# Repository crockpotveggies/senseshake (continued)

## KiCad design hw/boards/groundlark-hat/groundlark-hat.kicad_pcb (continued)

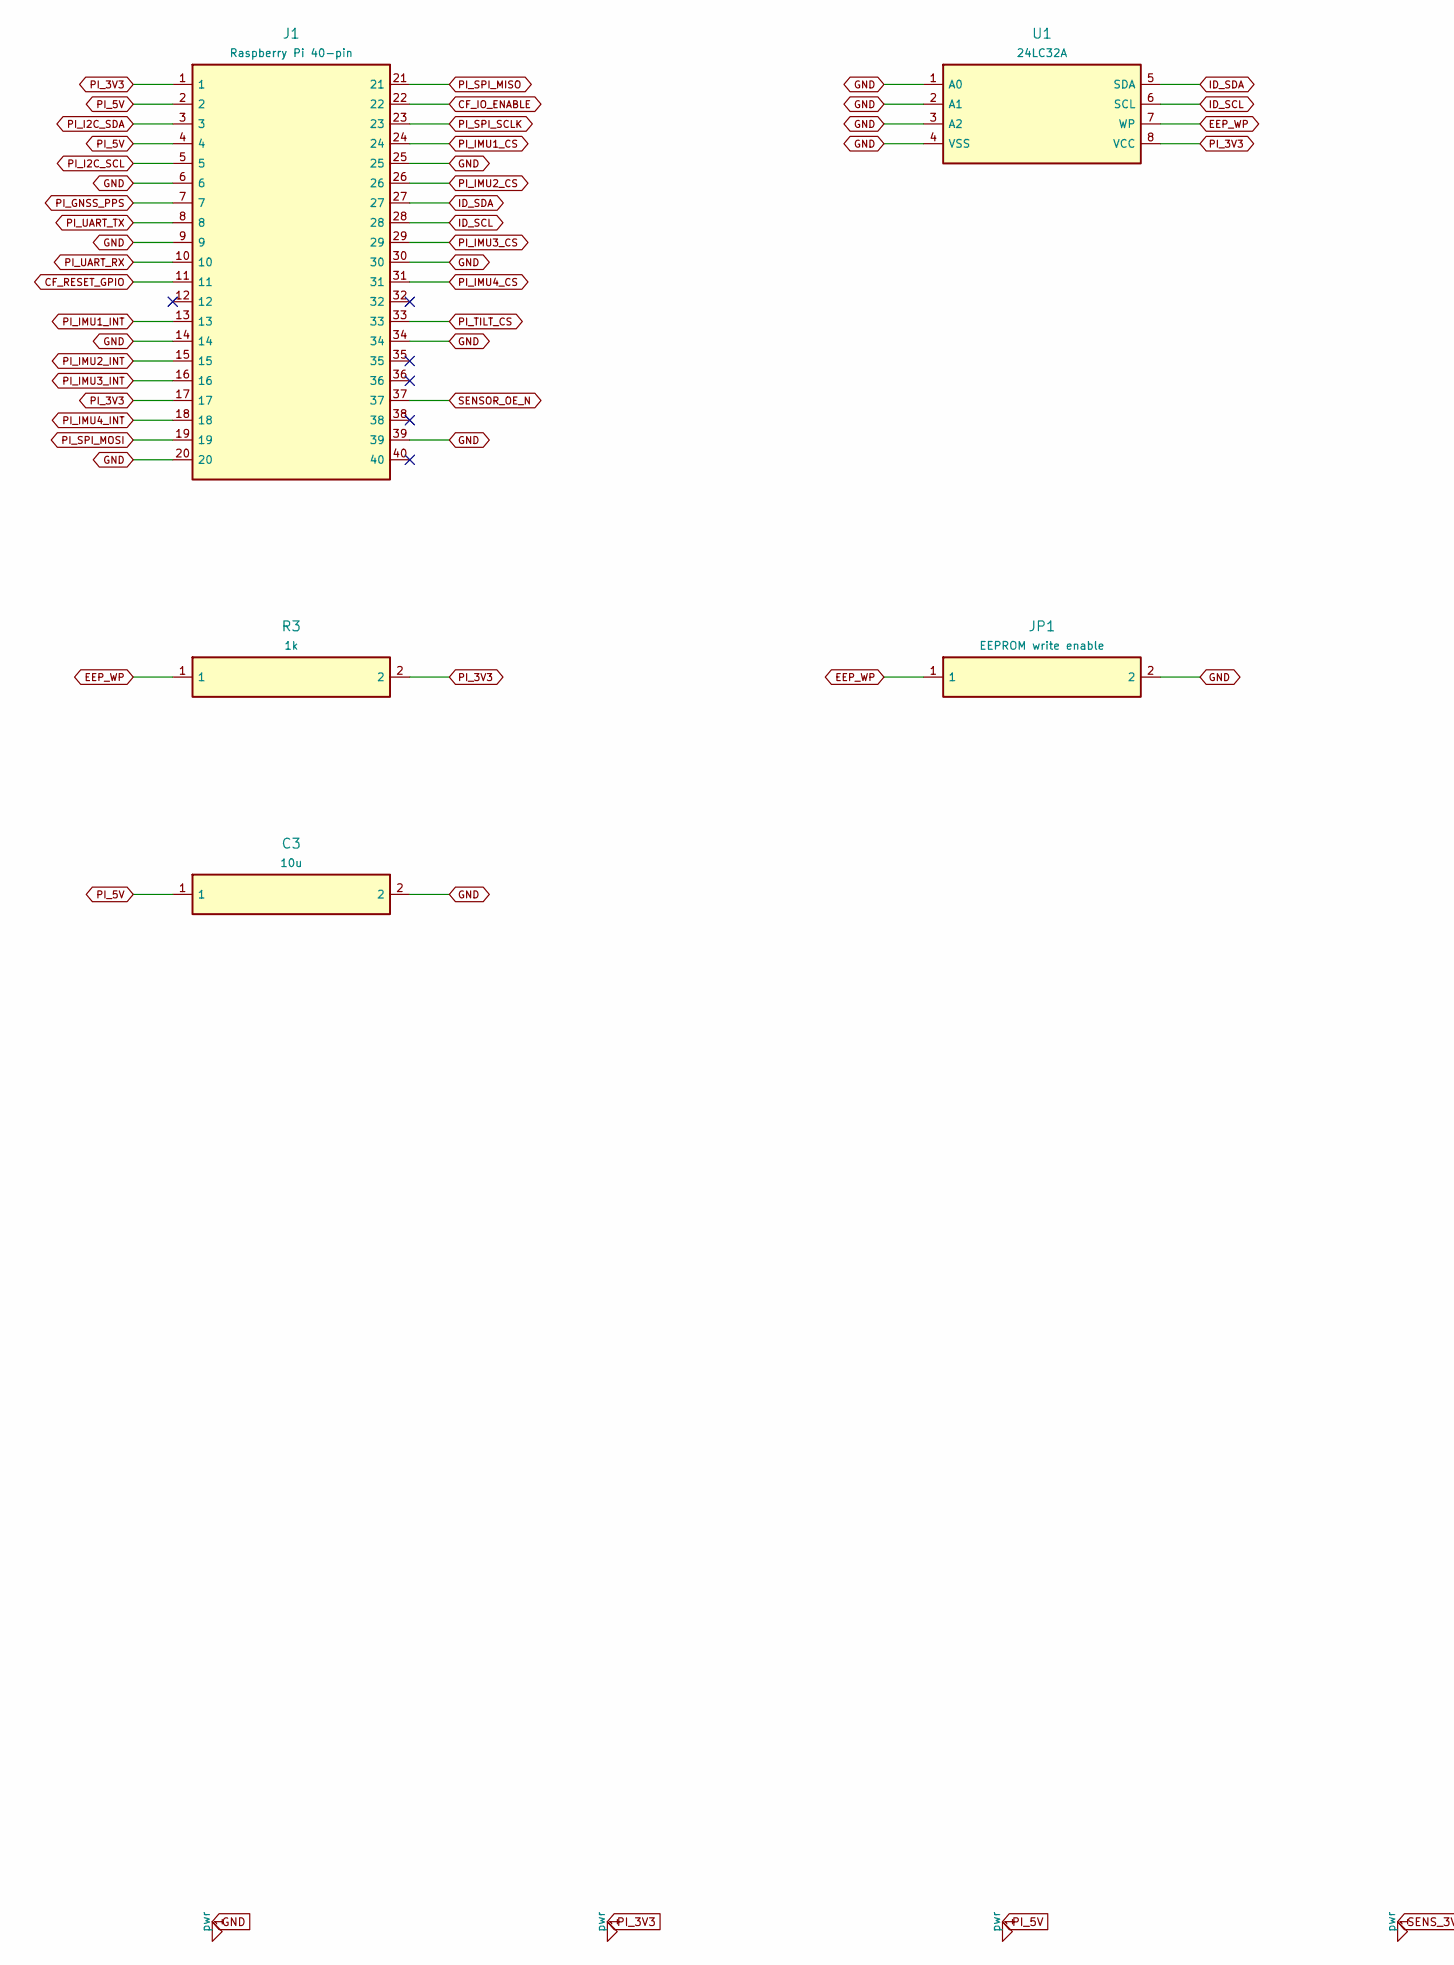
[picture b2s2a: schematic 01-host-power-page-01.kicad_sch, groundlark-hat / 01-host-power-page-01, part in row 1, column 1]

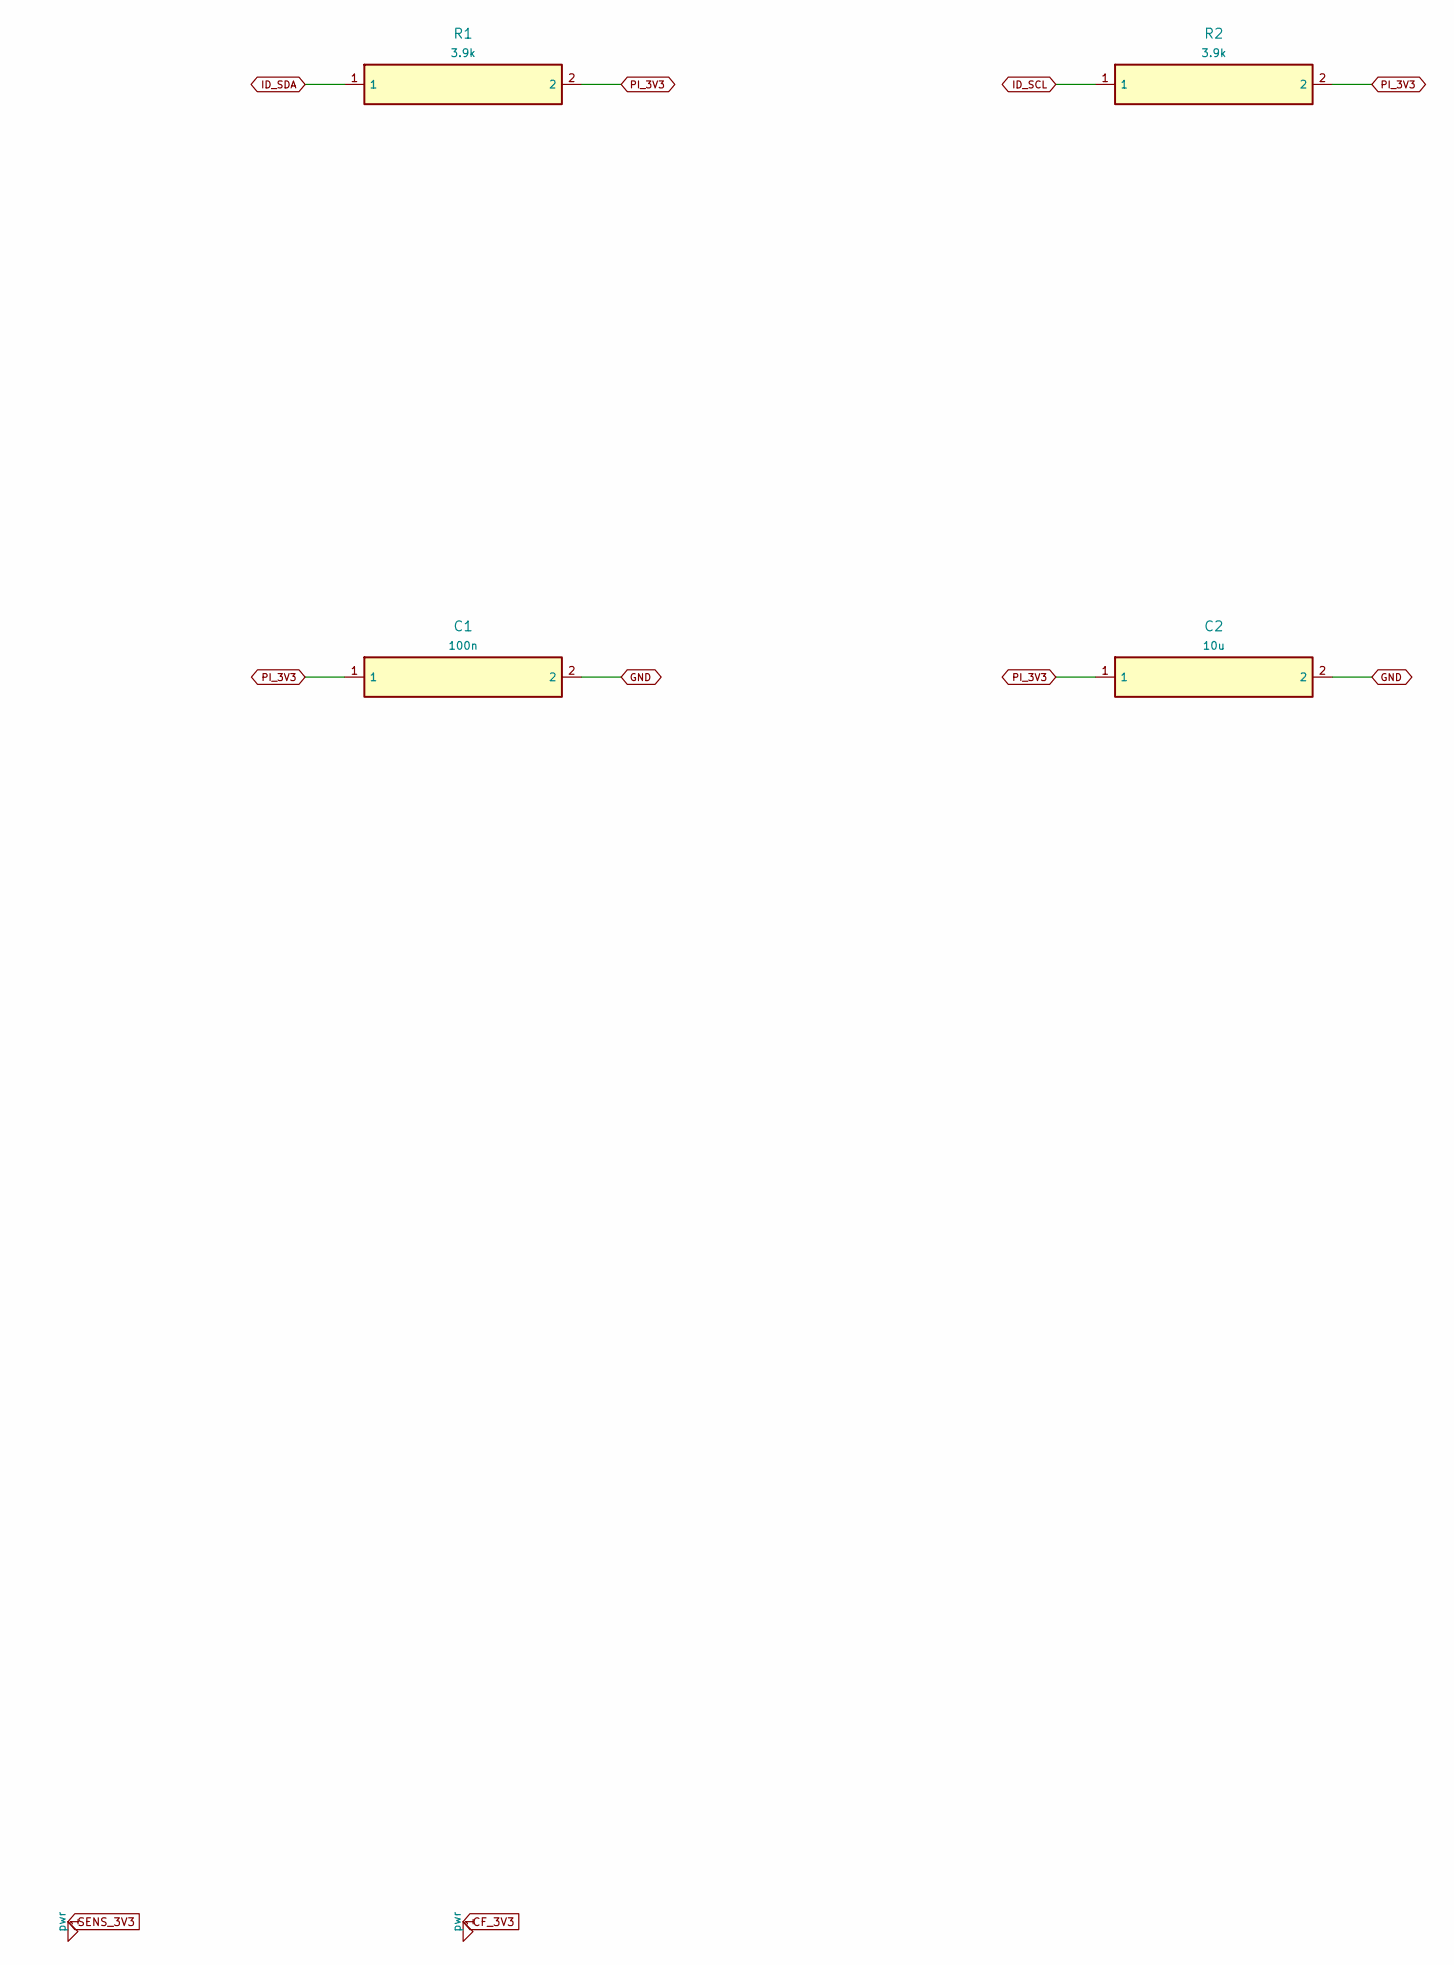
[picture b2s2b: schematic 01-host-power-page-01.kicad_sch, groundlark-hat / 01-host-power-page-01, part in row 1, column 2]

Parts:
C1: 100n; Capacitor_SMD__C_0603_1608Metric; MPN GRM188R71H104KA93D
C2, C3: 10u; Capacitor_SMD__C_0805_2012Metric; MPN GRM21BR61A106KE19L
J1: Raspberry Pi 40-pin; Connector_PinHeader_2.54mm__PinHeader_2x20_P2.54mm_Vertical; MPN Samtec ESQ-120-23-G-D
JP1: EEPROM write enable; Connector_PinHeader_2.54mm__PinHeader_1x02_P2.54mm_Vertical; MPN EEPROM write enable
R1, R2: 3.9k; Resistor_SMD__R_0603_1608Metric; MPN RC0603FR-073K9L
R3: 1k; Resistor_SMD__R_0603_1608Metric; MPN RC0603FR-071KL
U1: 24LC32A; Package_SO__SOIC-8_3.9x4.9mm_P1.27mm; MPN 24LC32A-I/SN

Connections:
12: J1.12
32: J1.32
35: J1.35
36: J1.36
38: J1.38
40: J1.40
CF_IO_ENABLE: J1.22; also elsewhere on the board
CF_RESET_GPIO: J1.11; also elsewhere on the board
EEP_WP: JP1.1, R3.1, U1.7 (WP)
GND: C1.2, C2.2, C3.2, J1.6, J1.9, J1.14, J1.20, J1.25, J1.30, J1.34, J1.39, JP1.2, U1.1 (A0), U1.2 (A1), U1.3 (A2), U1.4 (VSS); also elsewhere on the board
ID_SCL: J1.28, R2.1, U1.6 (SCL)
ID_SDA: J1.27, R1.1, U1.5 (SDA)
PI_3V3: C1.1, C2.1, J1.1, J1.17, R1.2, R2.2, R3.2, U1.8 (VCC); also elsewhere on the board
PI_5V: C3.1, J1.2, J1.4; also elsewhere on the board
PI_GNSS_PPS: J1.7; also elsewhere on the board
PI_I2C_SCL: J1.5; also elsewhere on the board
PI_I2C_SDA: J1.3; also elsewhere on the board
PI_IMU1_CS: J1.24; also elsewhere on the board
PI_IMU1_INT: J1.13; also elsewhere on the board
PI_IMU2_CS: J1.26; also elsewhere on the board
PI_IMU2_INT: J1.15; also elsewhere on the board
PI_IMU3_CS: J1.29; also elsewhere on the board
PI_IMU3_INT: J1.16; also elsewhere on the board
PI_IMU4_CS: J1.31; also elsewhere on the board
PI_IMU4_INT: J1.18; also elsewhere on the board
PI_SPI_MISO: J1.21; also elsewhere on the board
PI_SPI_MOSI: J1.19; also elsewhere on the board
PI_SPI_SCLK: J1.23; also elsewhere on the board
PI_TILT_CS: J1.33; also elsewhere on the board
PI_UART_RX: J1.10; also elsewhere on the board
PI_UART_TX: J1.8; also elsewhere on the board
SENSOR_OE_N: J1.37; also elsewhere on the board

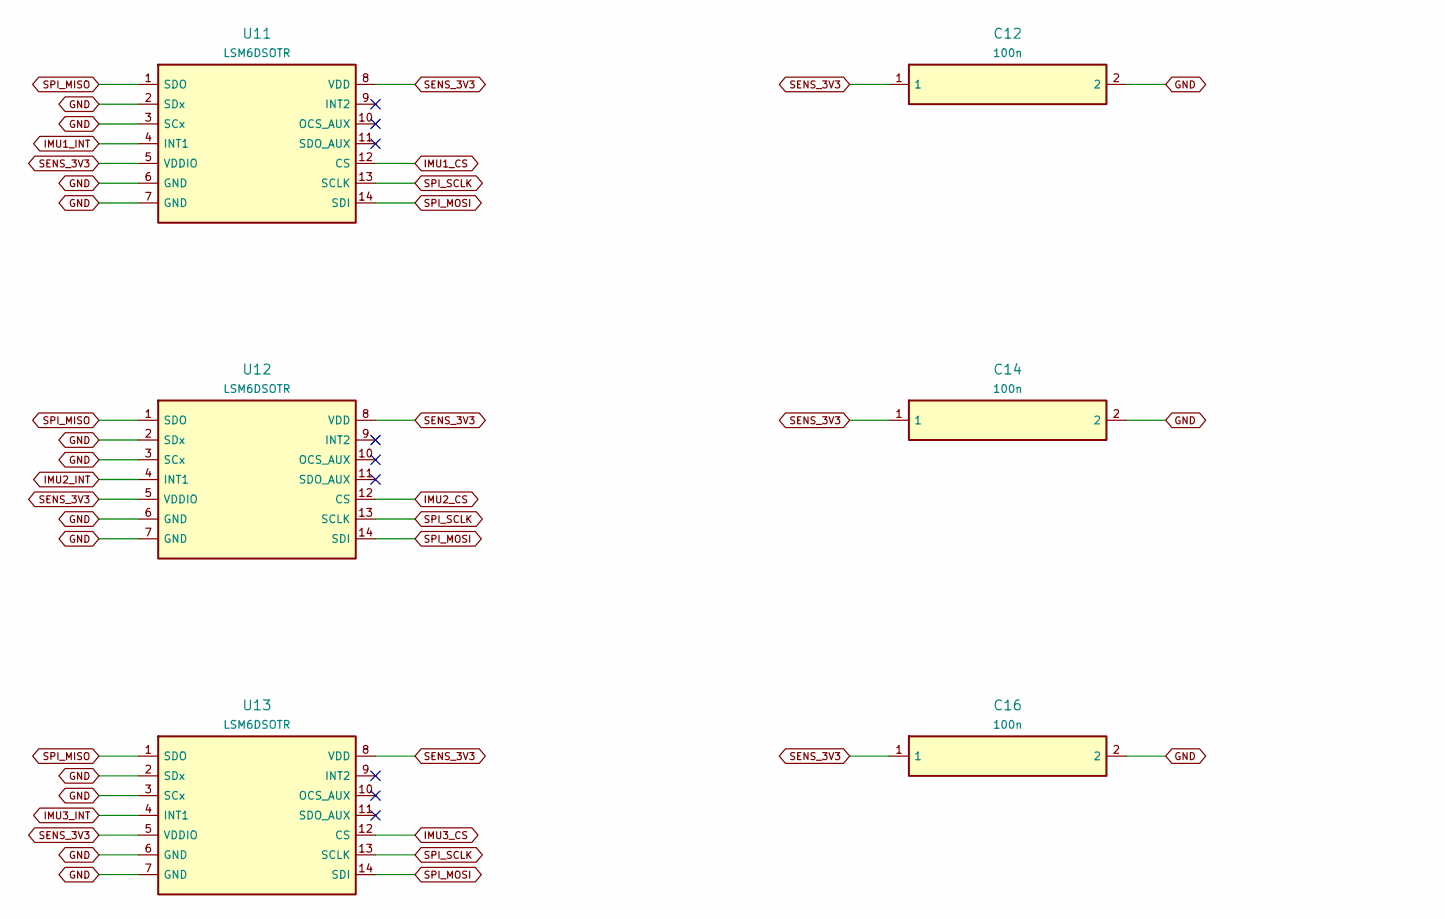
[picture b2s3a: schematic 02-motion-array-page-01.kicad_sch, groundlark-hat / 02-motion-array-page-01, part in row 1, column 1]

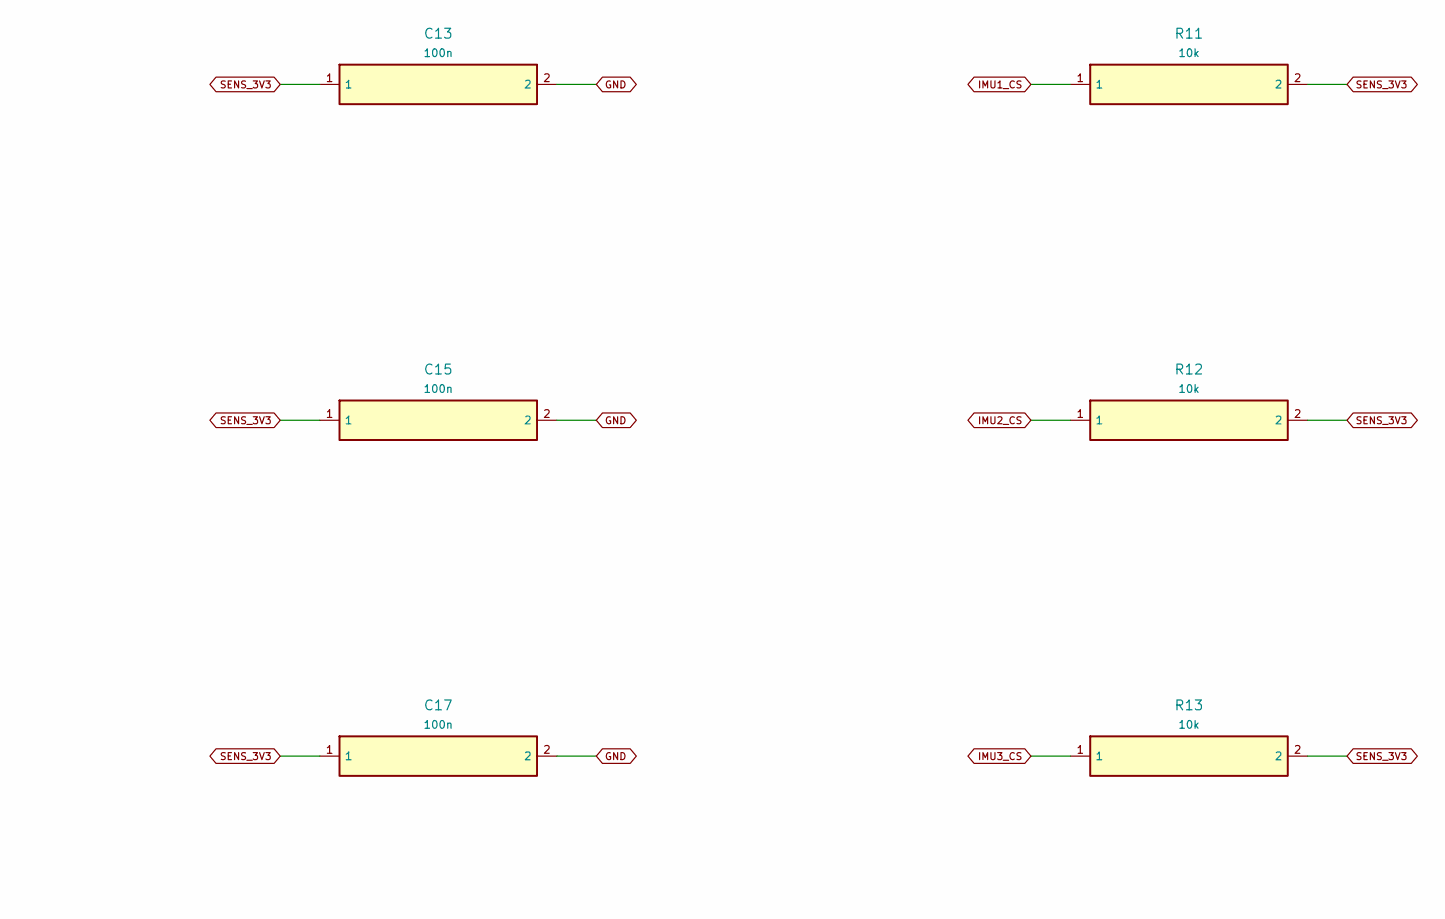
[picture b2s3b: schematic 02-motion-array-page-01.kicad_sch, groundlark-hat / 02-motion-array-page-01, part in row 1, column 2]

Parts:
C12, C13, C14, C15, C16, C17: 100n; Capacitor_SMD__C_0402_1005Metric; MPN GRM155R71C104KA88D
R11, R12, R13: 10k; Resistor_SMD__R_0603_1608Metric; MPN RC0603FR-0710KL
U11, U12, U13: LSM6DSOTR; Package_LGA__LGA-14_3x2.5mm_P0.5mm_LayoutBorder3x4y; MPN LSM6DSOTR

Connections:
9: U11.9 (INT2)
10: U11.10 (OCS_AUX)
11: U11.11 (SDO_AUX)
GND: C12.2, C13.2, C14.2, C15.2, C16.2, C17.2, U11.2 (SDx), U11.3 (SCx), U11.6 (GND), U11.7 (GND), U12.2 (SDx), U12.3 (SCx), U12.6 (GND), U12.7 (GND), U13.2 (SDx), U13.3 (SCx), U13.6 (GND), U13.7 (GND); also elsewhere on the board
IMU1_CS: R11.1, U11.12 (CS); also elsewhere on the board
IMU1_INT: U11.4 (INT1); also elsewhere on the board
IMU2_CS: R12.1, U12.12 (CS); also elsewhere on the board
IMU2_INT: U12.4 (INT1); also elsewhere on the board
IMU3_CS: R13.1, U13.12 (CS); also elsewhere on the board
IMU3_INT: U13.4 (INT1); also elsewhere on the board
SENS_3V3: C12.1, C13.1, C14.1, C15.1, C16.1, C17.1, R11.2, R12.2, R13.2, U11.5 (VDDIO), U11.8 (VDD), U12.5 (VDDIO), U12.8 (VDD), U13.5 (VDDIO), U13.8 (VDD); also elsewhere on the board
SPI_MISO: U11.1 (SDO), U12.1 (SDO), U13.1 (SDO); also elsewhere on the board
SPI_MOSI: U11.14 (SDI), U12.14 (SDI), U13.14 (SDI); also elsewhere on the board
SPI_SCLK: U11.13 (SCLK), U12.13 (SCLK), U13.13 (SCLK); also elsewhere on the board
u12-9: U12.9 (INT2)
u12-10: U12.10 (OCS_AUX)
u12-11: U12.11 (SDO_AUX)
u13-9: U13.9 (INT2)
u13-10: U13.10 (OCS_AUX)
u13-11: U13.11 (SDO_AUX)

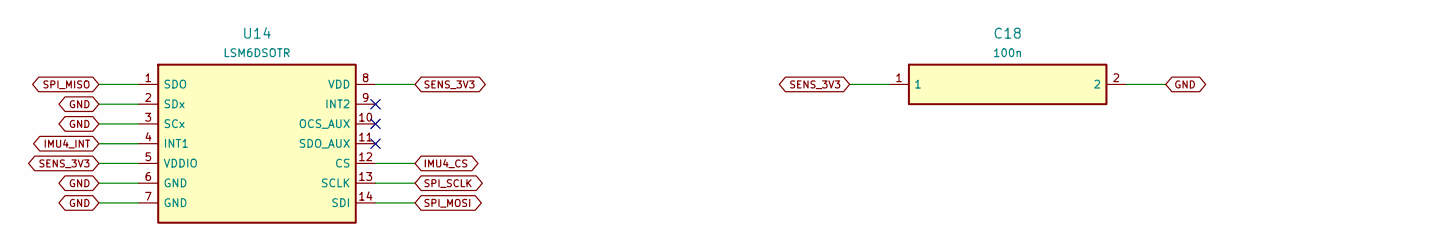
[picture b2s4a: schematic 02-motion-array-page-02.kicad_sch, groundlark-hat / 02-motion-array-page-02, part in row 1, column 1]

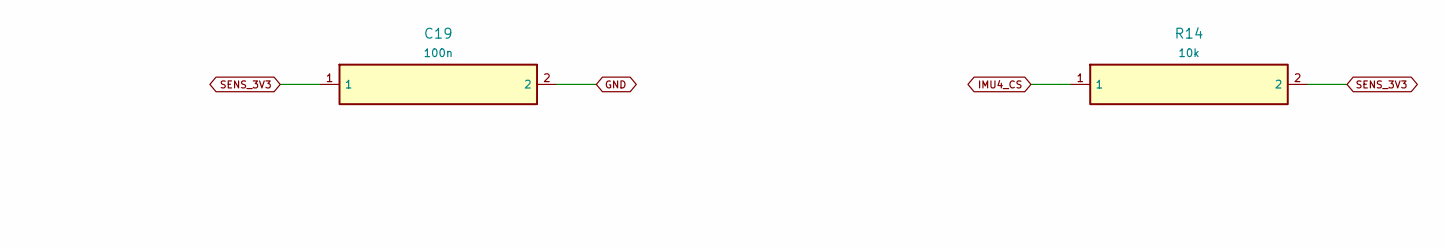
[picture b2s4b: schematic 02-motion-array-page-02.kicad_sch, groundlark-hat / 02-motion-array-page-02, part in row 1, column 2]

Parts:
C18, C19: 100n; Capacitor_SMD__C_0402_1005Metric; MPN GRM155R71C104KA88D
R14: 10k; Resistor_SMD__R_0603_1608Metric; MPN RC0603FR-0710KL
U14: LSM6DSOTR; Package_LGA__LGA-14_3x2.5mm_P0.5mm_LayoutBorder3x4y; MPN LSM6DSOTR

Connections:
GND: C18.2, C19.2, U14.2 (SDx), U14.3 (SCx), U14.6 (GND), U14.7 (GND); also elsewhere on the board
IMU4_CS: R14.1, U14.12 (CS); also elsewhere on the board
IMU4_INT: U14.4 (INT1); also elsewhere on the board
SENS_3V3: C18.1, C19.1, R14.2, U14.5 (VDDIO), U14.8 (VDD); also elsewhere on the board
SPI_MISO: U14.1 (SDO); also elsewhere on the board
SPI_MOSI: U14.14 (SDI); also elsewhere on the board
SPI_SCLK: U14.13 (SCLK); also elsewhere on the board
u14-9: U14.9 (INT2)
u14-10: U14.10 (OCS_AUX)
u14-11: U14.11 (SDO_AUX)

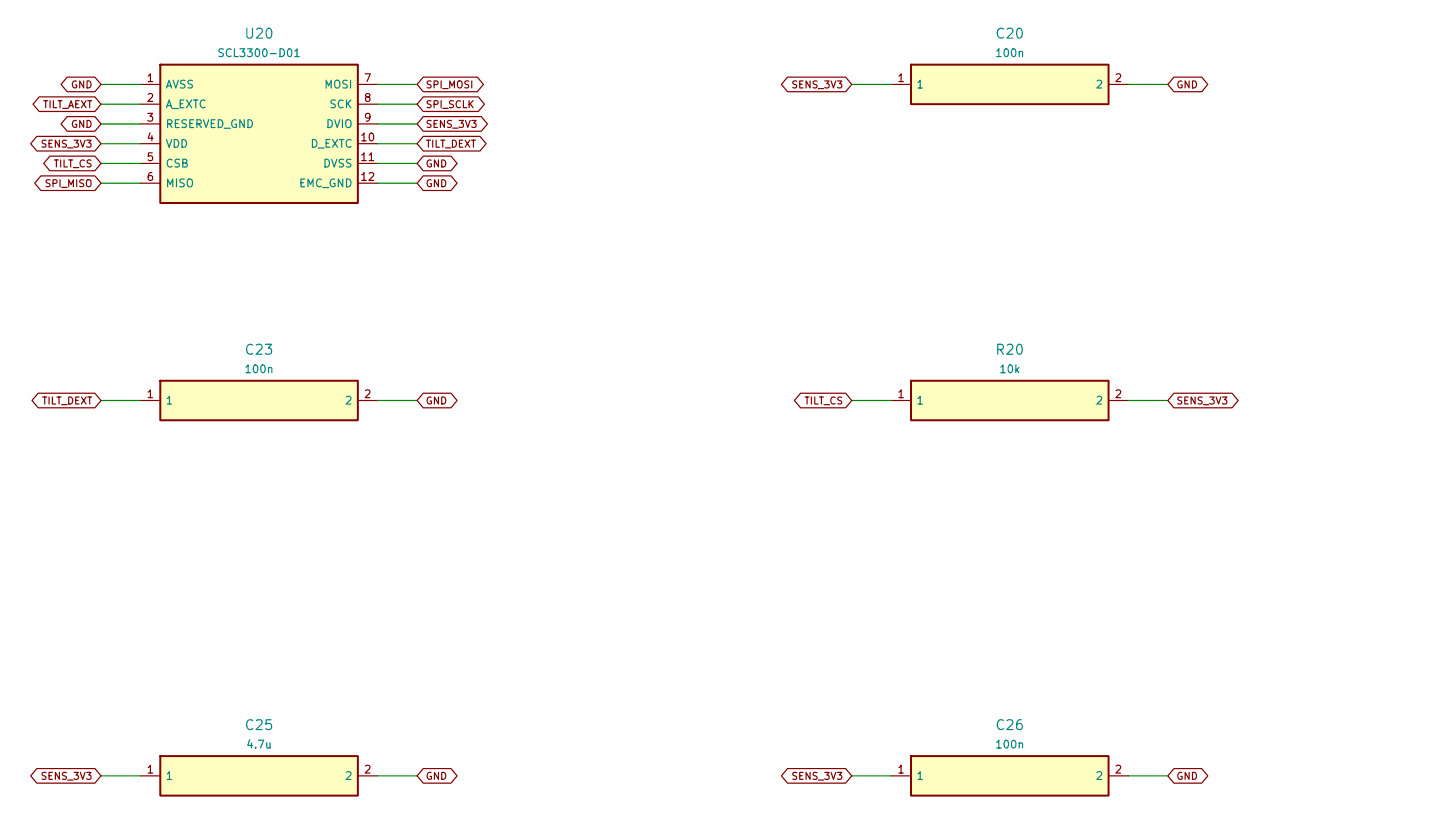
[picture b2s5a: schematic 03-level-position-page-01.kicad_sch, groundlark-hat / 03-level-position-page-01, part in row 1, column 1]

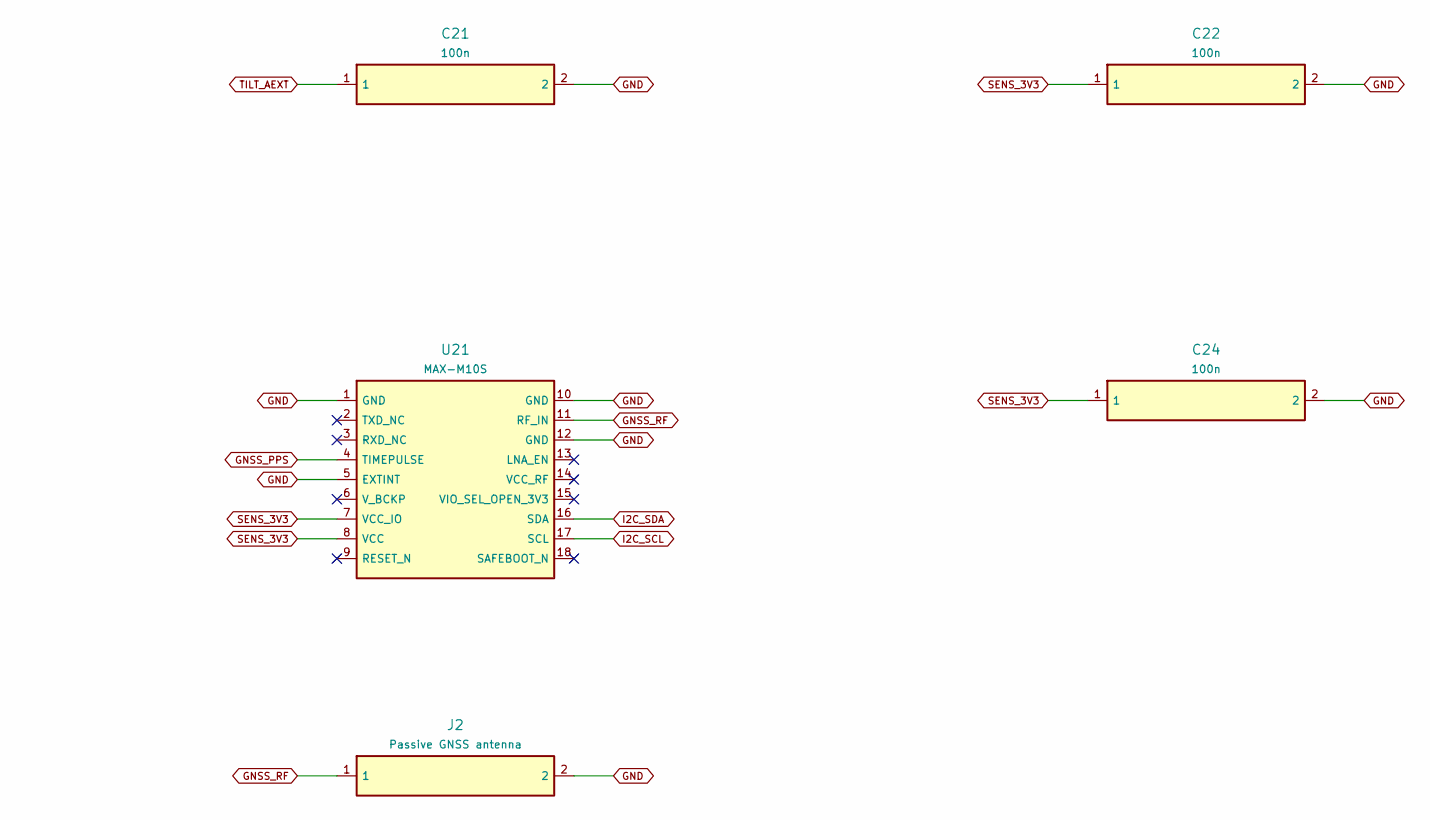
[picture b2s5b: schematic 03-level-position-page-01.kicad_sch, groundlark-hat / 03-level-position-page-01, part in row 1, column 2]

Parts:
C20, C21, C22, C23: 100n; Capacitor_SMD__C_0402_1005Metric; MPN GRM155R71C104KA88D
C24, C26: 100n; Capacitor_SMD__C_0603_1608Metric; MPN GRM188R71H104KA93D
C25: 4.7u; Capacitor_SMD__C_0805_2012Metric; MPN GRM21BR71A475KA73L
J2: Passive GNSS antenna; Connector_Coaxial__U.FL_Hirose_U.FL-R-SMT-1_Vertical; MPN U.FL-R-SMT-1(10)
R20: 10k; Resistor_SMD__R_0603_1608Metric; MPN RC0603FR-0710KL
U20: SCL3300-D01; Groundlark__SCL3300_D01; MPN SCL3300-D01-10
U21: MAX-M10S; RF_GPS__ublox_MAX; MPN MAX-M10S-00B

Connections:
2: U21.2 (TXD_NC)
3: U21.3 (RXD_NC)
6: U21.6 (V_BCKP)
13: U21.13 (LNA_EN)
14: U21.14 (VCC_RF)
15: U21.15 (VIO_SEL_OPEN_3V3)
18: U21.18 (SAFEBOOT_N)
GND: C20.2, C21.2, C22.2, C23.2, C24.2, C25.2, C26.2, J2.2, U20.1 (AVSS), U20.3 (RESERVED_GND), U20.11 (DVSS), U20.12 (EMC_GND), U21.1 (GND), U21.5 (EXTINT), U21.10 (GND), U21.12 (GND); also elsewhere on the board
GNSS_PPS: U21.4 (TIMEPULSE); also elsewhere on the board
GNSS_RF: J2.1, U21.11 (RF_IN)
I2C_SCL: U21.17 (SCL); also elsewhere on the board
I2C_SDA: U21.16 (SDA); also elsewhere on the board
SENS_3V3: C20.1, C22.1, C24.1, C25.1, C26.1, R20.2, U20.4 (VDD), U20.9 (DVIO), U21.7 (VCC_IO), U21.8 (VCC); also elsewhere on the board
SPI_MISO: U20.6 (MISO); also elsewhere on the board
SPI_MOSI: U20.7 (MOSI); also elsewhere on the board
SPI_SCLK: U20.8 (SCK); also elsewhere on the board
TILT_AEXT: C21.1, U20.2 (A_EXTC)
TILT_CS: R20.1, U20.5 (CSB); also elsewhere on the board
TILT_DEXT: C23.1, U20.10 (D_EXTC)
u21-9: U21.9 (RESET_N)

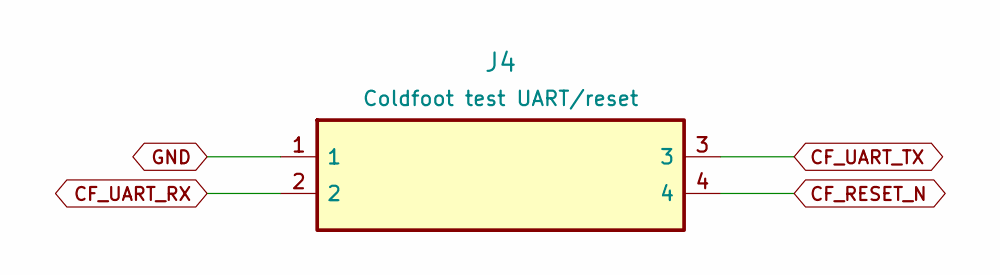
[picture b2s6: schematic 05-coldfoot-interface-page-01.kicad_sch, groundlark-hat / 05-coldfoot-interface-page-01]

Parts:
J4: Coldfoot test UART/reset; Connector_PinHeader_2.54mm__PinHeader_1x04_P2.54mm_Vertical; MPN Coldfoot UART service ONLY

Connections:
CF_RESET_N: J4.4; also elsewhere on the board
CF_UART_RX: J4.2; also elsewhere on the board
CF_UART_TX: J4.3; also elsewhere on the board
GND: J4.1; also elsewhere on the board

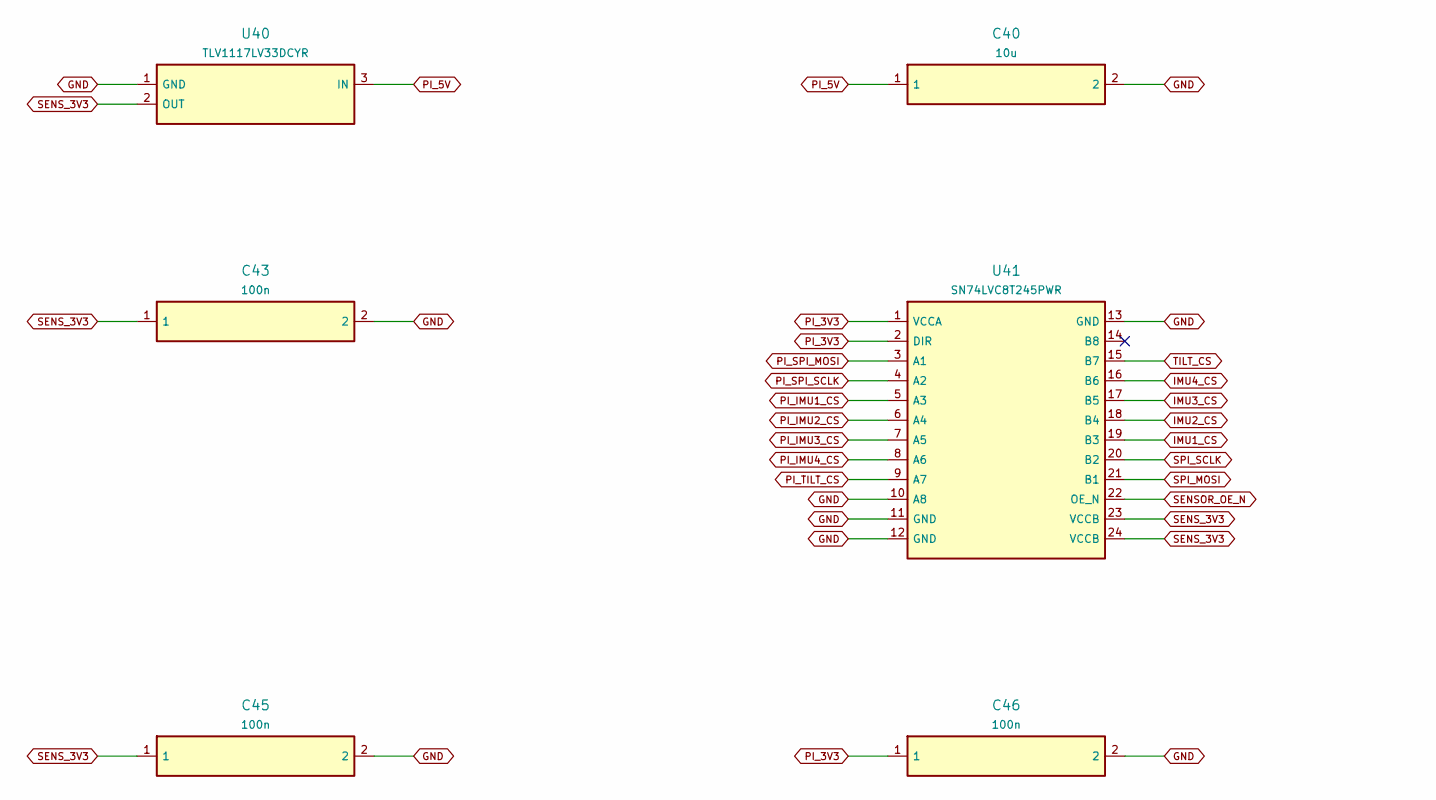
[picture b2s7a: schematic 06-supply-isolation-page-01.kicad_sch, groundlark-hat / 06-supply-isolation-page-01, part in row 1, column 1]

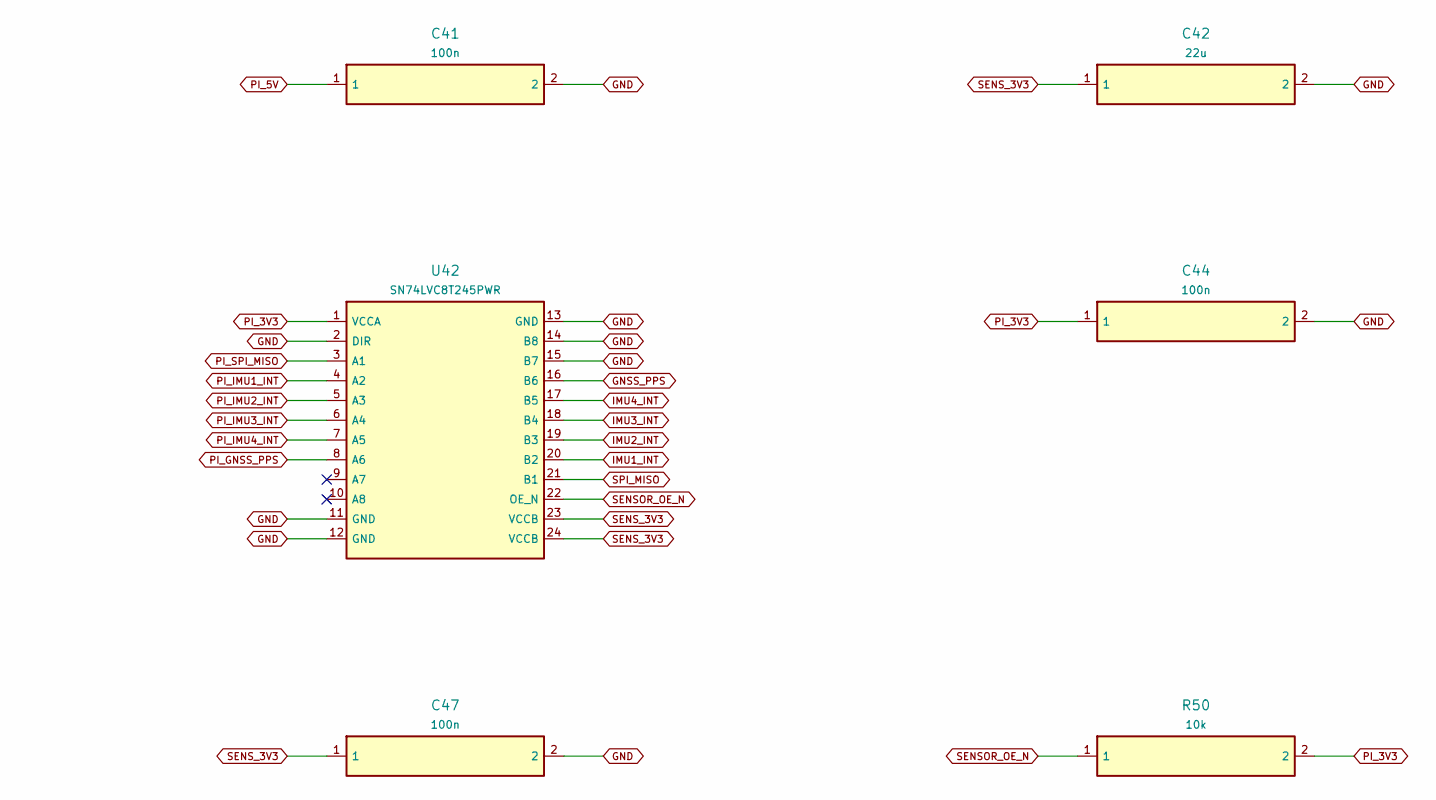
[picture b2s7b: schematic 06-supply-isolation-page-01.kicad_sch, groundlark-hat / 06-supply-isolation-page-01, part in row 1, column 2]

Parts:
C40: 10u; Capacitor_SMD__C_0805_2012Metric; MPN GRM21BR61A106KE19L
C41, C43, C44, C45, C46, C47: 100n; Capacitor_SMD__C_0603_1608Metric; MPN GRM188R71H104KA93D
C42: 22u; Capacitor_SMD__C_1206_3216Metric; MPN GRM31CR61A226KE19L
R50: 10k; Resistor_SMD__R_0603_1608Metric; MPN RC0603FR-0710KL
U40: TLV1117LV33DCYR; Package_TO_SOT_SMD__SOT-223-3_TabPin2; MPN TLV1117LV33DCYR
U41, U42: SN74LVC8T245PWR; Package_SO__TSSOP-24_4.4x7.8mm_P0.65mm; MPN SN74LVC8T245PWR

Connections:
GND: C40.2, C41.2, C42.2, C43.2, C44.2, C45.2, C46.2, C47.2, U40.1 (GND), U41.10 (A8), U41.11 (GND), U41.12 (GND), U41.13 (GND), U42.2 (DIR), U42.11 (GND), U42.12 (GND), U42.13 (GND), U42.14 (B8), U42.15 (B7); also elsewhere on the board
GNSS_PPS: U42.16 (B6); also elsewhere on the board
IMU1_CS: U41.19 (B3); also elsewhere on the board
IMU1_INT: U42.20 (B2); also elsewhere on the board
IMU2_CS: U41.18 (B4); also elsewhere on the board
IMU2_INT: U42.19 (B3); also elsewhere on the board
IMU3_CS: U41.17 (B5); also elsewhere on the board
IMU3_INT: U42.18 (B4); also elsewhere on the board
IMU4_CS: U41.16 (B6); also elsewhere on the board
IMU4_INT: U42.17 (B5); also elsewhere on the board
PI_3V3: C44.1, C46.1, R50.2, U41.1 (VCCA), U41.2 (DIR), U42.1 (VCCA); also elsewhere on the board
PI_5V: C40.1, C41.1, U40.3 (IN); also elsewhere on the board
PI_GNSS_PPS: U42.8 (A6); also elsewhere on the board
PI_IMU1_CS: U41.5 (A3); also elsewhere on the board
PI_IMU1_INT: U42.4 (A2); also elsewhere on the board
PI_IMU2_CS: U41.6 (A4); also elsewhere on the board
PI_IMU2_INT: U42.5 (A3); also elsewhere on the board
PI_IMU3_CS: U41.7 (A5); also elsewhere on the board
PI_IMU3_INT: U42.6 (A4); also elsewhere on the board
PI_IMU4_CS: U41.8 (A6); also elsewhere on the board
PI_IMU4_INT: U42.7 (A5); also elsewhere on the board
PI_SPI_MISO: U42.3 (A1); also elsewhere on the board
PI_SPI_MOSI: U41.3 (A1); also elsewhere on the board
PI_SPI_SCLK: U41.4 (A2); also elsewhere on the board
PI_TILT_CS: U41.9 (A7); also elsewhere on the board
SENSOR_OE_N: R50.1, U41.22 (OE_N), U42.22 (OE_N); also elsewhere on the board
SENS_3V3: C42.1, C43.1, C45.1, C47.1, U40.2 (OUT), U41.23 (VCCB), U41.24 (VCCB), U42.23 (VCCB), U42.24 (VCCB); also elsewhere on the board
SPI_MISO: U42.21 (B1); also elsewhere on the board
SPI_MOSI: U41.21 (B1); also elsewhere on the board
SPI_SCLK: U41.20 (B2); also elsewhere on the board
TILT_CS: U41.15 (B7); also elsewhere on the board
u41-14: U41.14 (B8)
u42-9: U42.9 (A7)
u42-10: U42.10 (A8)

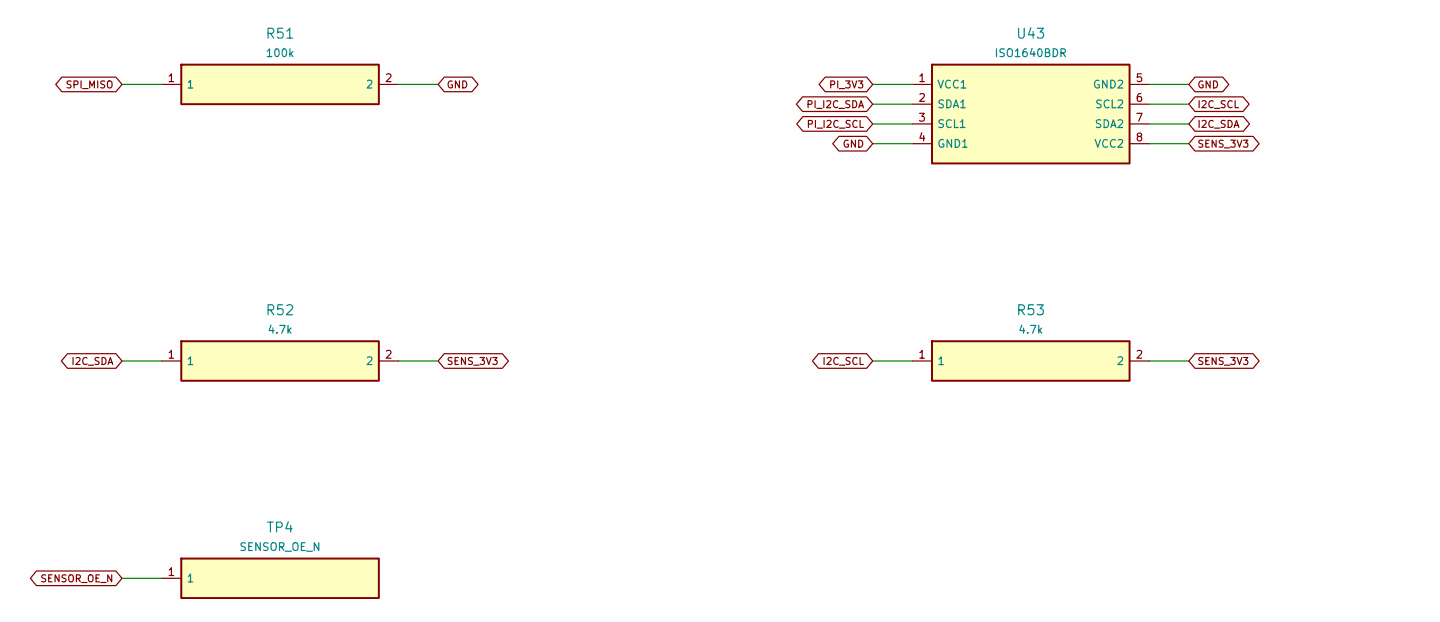
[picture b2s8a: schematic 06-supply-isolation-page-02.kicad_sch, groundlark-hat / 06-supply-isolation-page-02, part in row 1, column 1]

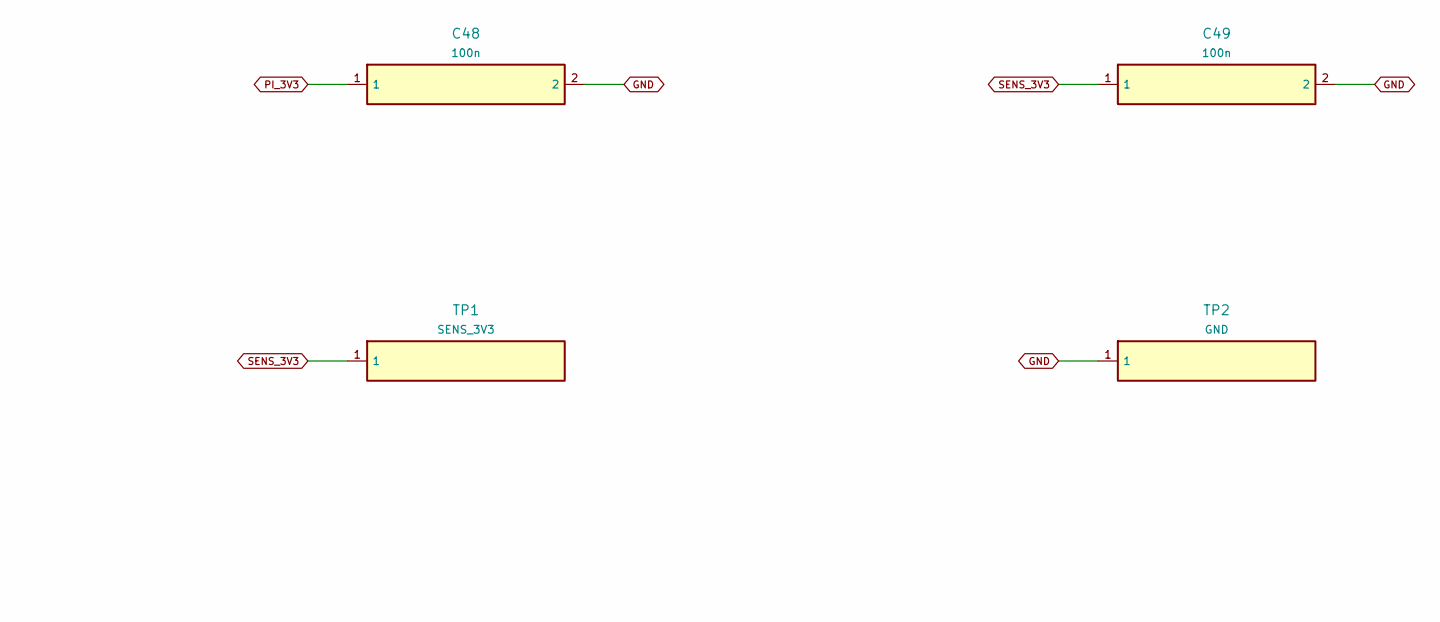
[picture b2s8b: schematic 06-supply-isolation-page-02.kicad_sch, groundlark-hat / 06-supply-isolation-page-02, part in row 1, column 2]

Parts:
C48, C49: 100n; Capacitor_SMD__C_0603_1608Metric; MPN GRM188R71H104KA93D
R51: 100k; Resistor_SMD__R_0603_1608Metric; MPN RC0603FR-07100KL
R52, R53: 4.7k; Resistor_SMD__R_0603_1608Metric; MPN RC0603FR-074K7L
TP1: SENS_3V3; TestPoint__TestPoint_Pad_D1.5mm; MPN SENS_3V3
TP2: GND; TestPoint__TestPoint_Pad_D1.5mm; MPN GND
TP4: SENSOR_OE_N; TestPoint__TestPoint_Pad_D1.5mm; MPN SENSOR_OE_N
U43: ISO1640BDR; Package_SO__SOIC-8_3.9x4.9mm_P1.27mm; MPN ISO1640BDR

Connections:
GND: C48.2, C49.2, R51.2, TP2.1, U43.4 (GND1), U43.5 (GND2); also elsewhere on the board
I2C_SCL: R53.1, U43.6 (SCL2); also elsewhere on the board
I2C_SDA: R52.1, U43.7 (SDA2); also elsewhere on the board
PI_3V3: C48.1, U43.1 (VCC1); also elsewhere on the board
PI_I2C_SCL: U43.3 (SCL1); also elsewhere on the board
PI_I2C_SDA: U43.2 (SDA1); also elsewhere on the board
SENSOR_OE_N: TP4.1; also elsewhere on the board
SENS_3V3: C49.1, R52.2, R53.2, TP1.1, U43.8 (VCC2); also elsewhere on the board
SPI_MISO: R51.1; also elsewhere on the board
